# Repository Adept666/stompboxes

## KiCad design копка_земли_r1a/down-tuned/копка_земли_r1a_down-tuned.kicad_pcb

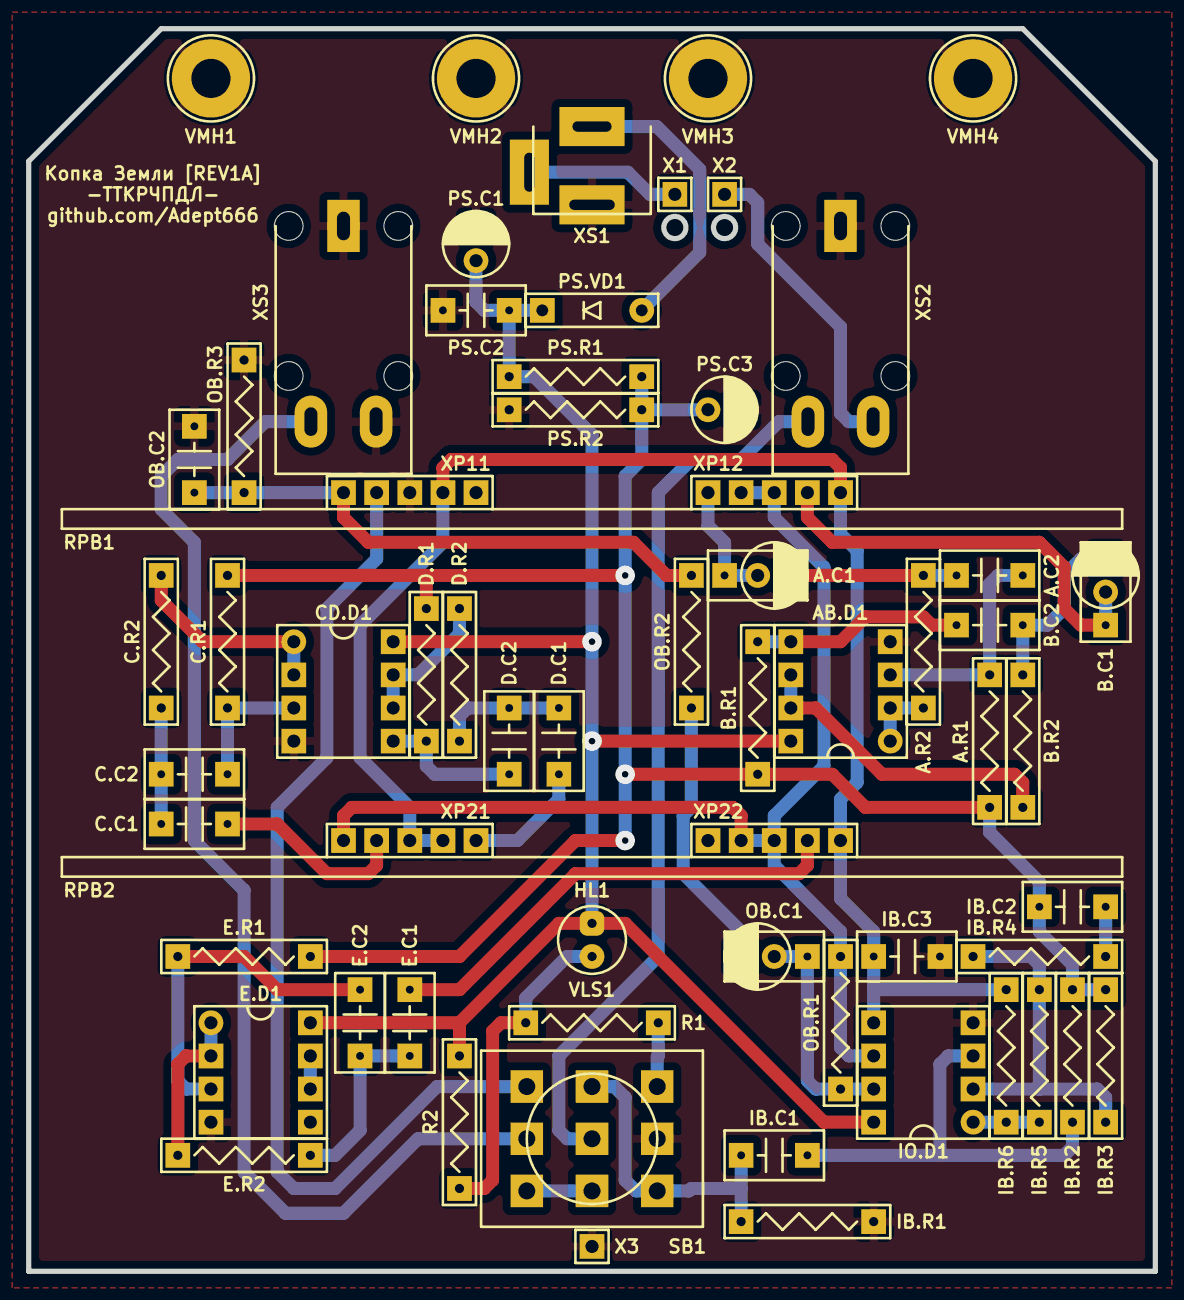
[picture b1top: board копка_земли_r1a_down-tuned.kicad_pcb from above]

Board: 2 copper layers, 86.4 x 95.3 mm, 63 parts (0 on the bottom side), 43 nets.

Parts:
A.C1: 225; C-DISK-D04.2-T03.0-P05.08-d0.5-OR-CP-RADIAL-D05.0-P02.0-CLS
A.C2: 473; C-DISK-D04.2-T03.0-P05.08-d0.5
A.R1: 124; R-MFR-25
A.R2: 471; R-MFR-25
AB.D1: 4558; P-DIP-08
B.C1: 105; C-DISK-D04.2-T03.0-P05.08-d0.5-OR-CP-RADIAL-D05.0-P02.0-CLS
B.C2: 333; C-DISK-D04.2-T03.0-P05.08-d0.5
B.R1: 104; R-MFR-25
B.R2: 471; R-MFR-25
C.C1: 154; C-DISK-D04.2-T03.0-P05.08-d0.5
C.C2: 682; C-DISK-D04.2-T03.0-P05.08-d0.5
C.R1: 104; R-MFR-25
C.R2: 102; R-MFR-25
CD.D1: 4558; P-DIP-08
D.C1: 683; C-DISK-D04.2-T03.0-P05.08-d0.5
D.C2: 332; C-DISK-D04.2-T03.0-P05.08-d0.5
D.R1: 104; R-MFR-25
D.R2: 102; R-MFR-25
E.C1: 223; C-DISK-D04.2-T03.0-P05.08-d0.5
E.C2: 681; C-DISK-D04.2-T03.0-P05.08-d0.5
E.D1: 4558; P-DIP-08
E.R1: 104; R-MFR-25
E.R2: 102; R-MFR-25
GB1: PP3; B-PP3-HV
HL1: FYL-5013UWC; LED-ROUND-05.0-UNI-SH-SPACER-PNL-5.3
IB.C1, IB.C2: 103; C-DISK-D04.2-T03.0-P05.08-d0.5
IB.C3: 151; C-DISK-D04.2-T03.0-P05.08-d0.5
IB.R1: 225; R-MFR-25
IB.R2: 474; R-MFR-25
IB.R3, IB.R5, IB.R6: 103; R-MFR-25
IB.R4: 102; R-MFR-25
IO.D1: 4558; P-DIP-08
OB.C1: 105; C-DISK-D04.2-T03.0-P05.08-d0.5-OR-CP-RADIAL-D05.0-P02.0-CLS
OB.C2: 103; C-DISK-D04.2-T03.0-P05.08-d0.5
OB.R1, OB.R2, OB.R3: 103; R-MFR-25
PS.C1: 107; CP-RADIAL-D05.0-P02.0-CLS
PS.C2: 104; C-DISK-D04.2-T03.0-P05.08-d0.5
PS.C3: 476; CP-RADIAL-D05.0-P02.0-CLS
PS.R1, PS.R2: 473; R-MFR-25
PS.VD1: 5817; P-DO-41
R1: 103; R-MFR-25
R2: X; R-MFR-25
RPB1, RPB2: B50K-B50K-B50K; RPB-1590BB-18-3x17-1.5-PNL-7.4-2.8
SB1: PBS-24-302SP; SW-PBS-24-302SP-2.5-PNL-13.0
VE1: 1590BB; 1590BB_B1
VLS1: BR-12.7; VLS-BR
VMH1, VMH2, VMH3, VMH4: DI5M3x18; VMH-STA-DA5-PNL-3.0
X1: +; CON-PAD-S-1.0-1.9
X2: -; CON-PAD-S-1.0-1.9
X3: COM; CON-PAD-S-1.0-1.9
XS1: DC-005; CON-DC-005
XS2, XS3: PJ-309; CON-ST-008X-04

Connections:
/BOOST-RAIL: IO.D1.6, OB.R1.1, RPB1.23, RPB1.33, RPB2.13, RPB2.23, RPB2.33
/CUT-RAIL: IB.C3.1, IB.R6.2, IO.D1.5, RPB1.21, RPB1.31, RPB2.11, RPB2.21, RPB2.31
/IN-CIR: IB.C1.1, IB.R1.2, SB1.NC3, SB1.NO2
/IN-CON: SB1.COM2, XS2.T
/LED: R1.1, SB1.NO3
/OUT-CIR: RPB1.12, SB1.NO1
/OUT-CON: SB1.COM1, XS3.T
/PP3-NEG: X2.1, XS2.R
/PP3-POS: X1.1, XS1.SN
COM: AB.D1.4, CD.D1.4, E.D1.4, IB.C3.2, IB.R1.1, IO.D1.4, OB.C2.2, OB.R3.1, PS.C1.-, PS.C2.2, PS.C3.-, PS.R2.1, RPB1.11, SB1.COM3, VMH1.0, VMH2.0, VMH3.0, VMH4.0, X3.1, XS1.C, XS2.S, XS3.R, XS3.S
unnamed: A.C1.+, RPB1.22
unnamed: A.C1.-, A.C2.1, A.R2.1
unnamed: A.C2.2, A.R1.2, AB.D1.3
unnamed: A.R2.2, AB.D1.1, AB.D1.2
unnamed: AB.D1.5, B.C2.2, B.R1.2
unnamed: AB.D1.6, AB.D1.7, B.R2.2
unnamed: B.C1.+, RPB1.32
unnamed: B.C1.-, B.C2.1, B.R2.1
unnamed: C.C1.1, RPB2.12
unnamed: C.C1.2, C.C2.1, C.R2.1
unnamed: C.C2.2, C.R1.2, CD.D1.3
unnamed: C.R2.2, CD.D1.1, CD.D1.2
unnamed: CD.D1.5, D.C2.2, D.R1.2
unnamed: CD.D1.6, CD.D1.7, D.R2.2
unnamed: D.C1.1, RPB2.22
unnamed: D.C1.2, D.C2.1, D.R2.1
unnamed: E.C1.1, RPB2.32
unnamed: E.C1.2, E.C2.1, E.R2.1
unnamed: E.C2.2, E.D1.3, E.R1.2
unnamed: E.D1.1, E.D1.2, E.R2.2
unnamed: E.D1.6, E.D1.7
unnamed: HL1.C, R1.2, R2.1
unnamed: IB.C1.2, IB.R2.2, IO.D1.3
unnamed: IB.C2.2, IB.R4.1
unnamed: IB.R3.2, IB.R4.2, IB.R5.1, IO.D1.2
unnamed: IB.R5.2, IB.R6.1, IO.D1.1
unnamed: IO.D1.7, OB.C1.+, OB.R1.2
unnamed: OB.C1.-, OB.R2.1
unnamed: OB.C2.1, OB.R2.2, OB.R3.2, RPB1.13
unnamed: PS.VD1.A, XS1.S
unnamed: SB1.NC1, SB1.NC2
V: AB.D1.8, CD.D1.8, E.D1.8, HL1.A, IO.D1.8, PS.C1.+, PS.C2.1, PS.R1.2, PS.VD1.C, R2.2
VREF: A.R1.1, B.R1.1, C.R1.1, D.R1.1, E.R1.1, IB.C2.1, IB.R2.1, IB.R3.1, PS.C3.+, PS.R1.1, PS.R2.2

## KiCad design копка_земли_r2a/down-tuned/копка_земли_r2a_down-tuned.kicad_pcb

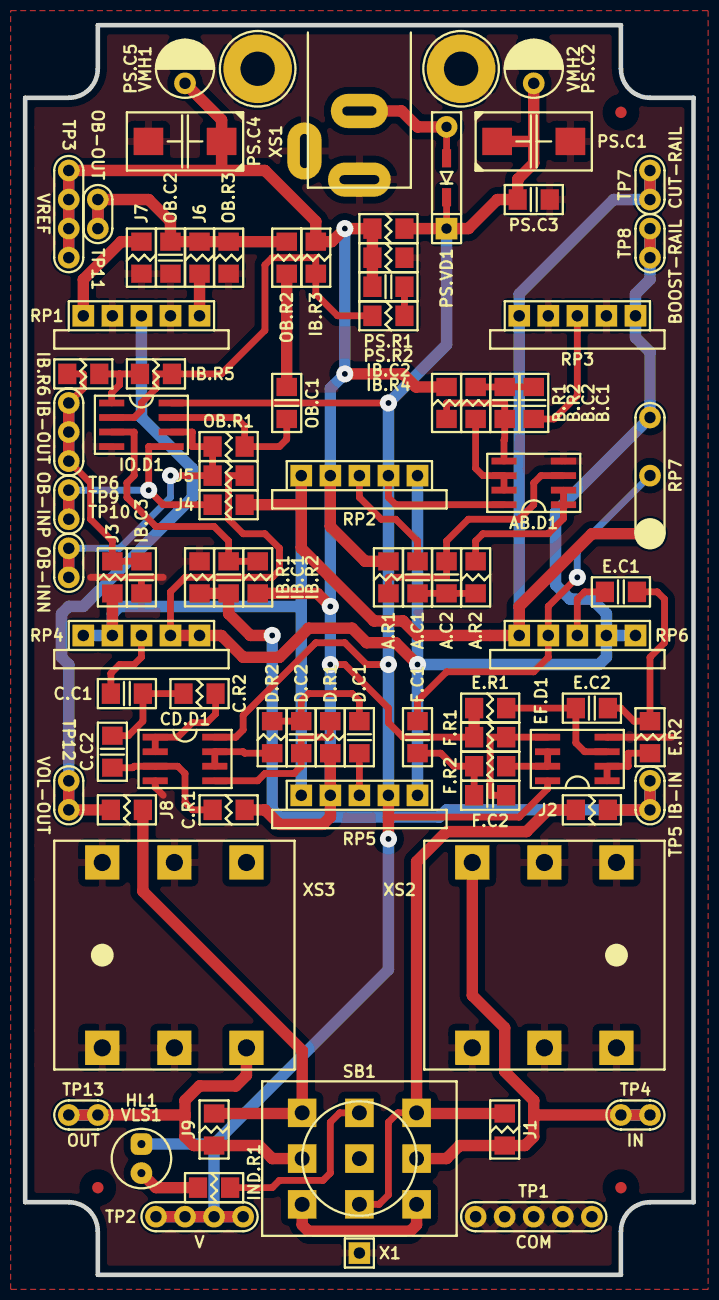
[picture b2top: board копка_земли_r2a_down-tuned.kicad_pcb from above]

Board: 2 copper layers, 58.4 x 109.2 mm, 93 parts (0 on the bottom side), 51 nets.

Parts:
A.C1: 225; C-SM-1206
A.C2: 473; C-SM-1206
A.R1: 124; R-SM-1206
A.R2: 471; R-SM-1206
AB.D1: 4558; P-SO-08
B.C1: 105; C-SM-1206
B.C2: 333; C-SM-1206
B.R1: 104; R-SM-1206
B.R2: 471; R-SM-1206
C.C1: 154; C-SM-1206
C.C2: 682; C-SM-1206
C.R1: 104; R-SM-1206
C.R2: 102; R-SM-1206
CD.D1: 4558; P-SO-08
D.C1: 683; C-SM-1206
D.C2: 332; C-SM-1206
D.R1: 104; R-SM-1206
D.R2: 102; R-SM-1206
E.C1: 223; C-SM-1206
E.C2: 681; C-SM-1206
E.R1: 104; R-SM-1206
E.R2: 102; R-SM-1206
EF.D1: 4558; P-SO-08
F.C1, F.C2: X; C-SM-1206
F.R1, F.R2: X; R-SM-1206
HL1: FYL-5013UWC; LED-ROUND-05.0-UNI-SH-SPACER-PNL-5.3
IB.C1, IB.C2: 103; C-SM-1206
IB.C3: 151; C-SM-1206
IB.R1: 225; R-SM-1206
IB.R2: 474; R-SM-1206
IB.R3, IB.R5, IB.R6: 103; R-SM-1206
IB.R4: 102; R-SM-1206
IND.R1: 103; R-SM-1206
IO.D1: 4558; P-SO-08
J1, J9: X; R-SM-1206
J2, J3, J4, J5, J6, J7, J8: 0; R-SM-1206
OB.C1: 105; C-SM-1206
OB.C2: 103; C-SM-1206
OB.R1, OB.R2, OB.R3: 103; R-SM-1206
PS.C1: 107; CP-CTSMD-D
PS.C2: 107; CP-RADIAL-D05.0-P02.0-CLS
PS.C3: 104; C-SM-1206
PS.C4: 476; CP-CTSMD-D
PS.C5: 476; CP-RADIAL-D05.0-P02.0-CLS
PS.R1, PS.R2: 473; R-SM-1206
PS.VD1: 0520; P-SOD-123-OR-DO-41
RP1, RP2, RP3, RP4, RP5, RP6: B50K; RPB-18-1x17-1.6-PNL-7.4-2.8
RP7: X; RP-EXTERNAL
SB1: PBS-24-302SP; SW-PBS-24-302SP-2.5-PNL-13.0
TP1: COM; TP-5-1.0-1.9
TP2: V; TP-4-1.0-1.9
TP3: VREF; TP-4-1.0-1.9
TP4: IN; TP-2-1.0-1.9
TP5: IB-IN; TP-2-1.0-1.9
TP6: IB-OUT; TP-3-1.0-1.9
TP7: CUT-RAIL; TP-2-1.0-1.9
TP8: BOOST-RAIL; TP-2-1.0-1.9
TP9: OB-INP; TP-2-1.0-1.9
TP10: OB-INN; TP-2-1.0-1.9
TP11: OB-OUT; TP-2-1.0-1.9
TP12: VOL-OUT; TP-2-1.0-1.9
TP13: OUT; TP-2-1.0-1.9
VE1: B013; B013_F1
VFM1, VFM2, VFM3: 1.0; VFM-1.0-3.0-SL
VLS1: BR-12.7; VLS-BR
VMH1, VMH2: DI5M3x18; VMH-STA-DA5-PNL-3.0
X1: COM; CON-PAD-S-1.0-1.9
XS1: DC-005; CON-DC-005-9V-OVAL
XS2, XS3: PJ-644C; CON-PJ-644C-IN-OR-OUT

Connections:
/BOOST-RAIL: J5.1, RP2.3, RP3.3, RP4.3, RP4.NC2, RP5.3, RP6.3, RP6.NC2, RP7.3, TP8.1
/CIR-IN: J1.2, J2.1, SB1.NC2, SB1.NO3
/CIR-OUT: J8.2, J9.1, SB1.NO1
/CUT-RAIL: J3.2, J4.1, RP2.1, RP3.1, RP4.1, RP4.NC1, RP5.1, RP6.1, RP7.1, TP7.1
/IB-IN: IB.C1.1, IB.R1.2, J2.2, TP5.1
/IB-OUT: IB.C3.1, IB.R6.2, J3.1, TP6.1
/IN: J1.1, SB1.COM3, TP4.1, XS2.T
/LED: IND.R1.1, SB1.NO2
/OB-INN: IO.D1.6, J5.2, OB.R1.1, TP10.1
/OB-INP: IO.D1.5, J4.2, TP9.1
/OB-OUT: J6.1, OB.C2.1, OB.R2.2, OB.R3.2, TP11.1
/OUT: J9.2, SB1.COM1, TP13.1, XS3.T
/VOL-COM: J7.1, RP1.1
/VOL-IN: J6.2, RP1.3
/VOL-OUT: J8.1, RP1.2, TP12.1
COM: AB.D1.4, CD.D1.4, EF.D1.4, IB.C3.2, IB.R1.1, IO.D1.4, J7.2, OB.C2.2, OB.R3.1, PS.C1.-, PS.C2.-, PS.C3.2, PS.C4.-, PS.C5.-, PS.R2.1, RP1.NC1, RP1.NC2, RP3.NC1, RP3.NC2, SB1.COM2, TP1.1, VMH1.0, VMH2.0, X1.1, XS1.C, XS1.SN, XS2.R, XS2.RN, XS2.S, XS2.SN, XS2.TN, XS3.R, XS3.RN, XS3.S, XS3.SN
unnamed: A.C1.1, RP2.2
unnamed: A.C1.2, A.C2.1, A.R2.1
unnamed: A.C2.2, A.R1.2, AB.D1.3
unnamed: A.R2.2, AB.D1.1, AB.D1.2
unnamed: AB.D1.5, B.C2.2, B.R1.2
unnamed: AB.D1.6, AB.D1.7, B.R2.2
unnamed: B.C1.1, RP3.2
unnamed: B.C1.2, B.C2.1, B.R2.1
unnamed: C.C1.1, RP4.2
unnamed: C.C1.2, C.C2.1, C.R2.1
unnamed: C.C2.2, C.R1.2, CD.D1.3
unnamed: C.R2.2, CD.D1.1, CD.D1.2
unnamed: CD.D1.5, D.C2.2, D.R1.2
unnamed: CD.D1.6, CD.D1.7, D.R2.2
unnamed: D.C1.1, RP5.2
unnamed: D.C1.2, D.C2.1, D.R2.1
unnamed: E.C1.1, RP6.2
unnamed: E.C1.2, E.C2.1, E.R2.1
unnamed: E.C2.2, E.R1.2, EF.D1.3
unnamed: E.R2.2, EF.D1.1, EF.D1.2
unnamed: EF.D1.5, F.C2.2, F.R1.2
unnamed: EF.D1.6, EF.D1.7, F.R2.2
unnamed: F.C1.1, RP6.NC1, RP7.2
unnamed: F.C1.2, F.C2.1, F.R2.1
unnamed: HL1.C, IND.R1.2
unnamed: IB.C1.2, IB.R2.2, IO.D1.3
unnamed: IB.C2.2, IB.R4.1
unnamed: IB.R3.2, IB.R4.2, IB.R5.1, IO.D1.2
unnamed: IB.R5.2, IB.R6.1, IO.D1.1
unnamed: IO.D1.7, OB.C1.1, OB.R1.2
unnamed: OB.C1.2, OB.R2.1
unnamed: PS.VD1.A, XS1.S
unnamed: SB1.NC1, SB1.NC3
V: AB.D1.8, CD.D1.8, EF.D1.8, HL1.A, IO.D1.8, PS.C1.+, PS.C2.+, PS.C3.1, PS.R1.2, PS.VD1.C, RP2.NC2, RP5.NC2, TP2.1
VREF: A.R1.1, B.R1.1, C.R1.1, D.R1.1, E.R1.1, F.R1.1, IB.C2.1, IB.R2.1, IB.R3.1, PS.C4.+, PS.C5.+, PS.R1.1, PS.R2.2, RP2.NC1, RP5.NC1, TP3.1

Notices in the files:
копка_земли_r1a/down-tuned/копка_земли_r1a_down-tuned.kicad_pcb:
This project is licensed under GNU General Public License v3.0 or later
